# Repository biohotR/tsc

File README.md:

# OpenBook

## Overview

The project was carried out as part of the Computer Systems Testing course and aims to create a detailed 3D model of an E-Book Reader tablet. We worked on both the internal circuit design and the development of the device’s external appearance, using Fusion 360 software provided by Autodesk.

## Bill of Materials
| Componenta | Link | Datasheet |
|-----------|--------------|-----------|
| BUTTON | [Model](https://industry.panasonic.com/global/en/products/control/switch/light-touch/number/evqpuj02k) | [Datasheet](https://www.lcsc.com/datasheet/lcsc_datasheet_2201121800_PANASONIC-EVQPUJ02K_C2936858.pdf) |
| CAPACITOR | [Model](https://componentsearchengine.com/part-view/R0402%201%25%20100%20K%20(RC0402FR-07100KL)/YAGEO) | [Datasheet](//efaidnbmnnnibpcajpcglclefindmkaj/https://www.resistor.com/assets/pdf/0402tstd.pdf) |
| CPH3225A | [Model](https://www.snapeda.com/parts/CPH3225A/Seiko+Instruments/view-part/?ref=eda) | [Datasheet](https://octopart.com/datasheet/cph3225a-seiko-25340571) |
| EVQPUJ02K | [Model](https://industry.panasonic.com/global/en/products/control/switch/light-touch/number/evqpuj02k) | [Datasheet](https://www.lcsc.com/datasheet/lcsc_datasheet_2201121800_PANASONIC-EVQPUJ02K_C2936858.pdf) |
| KP-1608SURCK | [Model](https://www.snapeda.com/parts/KP-1608SURCK/Kingbright/view-part/?ref=search&t=LED%200603) | [Datasheet](//efaidnbmnnnibpcajpcglclefindmkaj/https://media.elv.com/file/107153_led_surck1608_data.pdf) |
| USBLC6-2SC6Y | [Model](https://www.snapeda.com/parts/USBLC6-2SC6Y/STMicroelectronics/view-part/?ref=eda) | [Datasheet](https://www.digikey.com/en/htmldatasheets/production/1375342/0/0/1/usblc6-2sc6y) |
| SD0805S020S1R0 | [Model](https://ro.mouser.com/ProductDetail/KYOCERA-AVX/SD0805S020S1R0?qs=jCA%252BPfw4LHbpkAoSnwrdjw%3D%3D) | [Datasheet](https://www.alldatasheet.com/view.jsp?Searchword=SD0805S&sField=2) |
| PGB1010603MR | [Model](https://www.snapeda.com/parts/PGB1010603MR/Littelfuse/view-part/?ref=eda) | [Datasheet](https://www.alldatasheet.com/view.jsp?Searchword=Pgb1010603mr&gad_source=1&gbraid=0AAAAADcdDU8aYfZtfJfdZ9I5j6RwZ_cbA&gclid=Cj0KCQjwqcO_BhDaARIsACz62vOPBOBe0eOh5gDUFkkKl4JBcbmoFZYtJ8BOnbaWqr_BuUCcVWvbutAaAmGkEALw_wcB) |
| BD5229G-TR  | [Model](https://componentsearchengine.com/part-view/BD5229G-TR/ROHM%20Semiconductor) | [Datasheet](https://www.lcsc.com/datasheet/lcsc_datasheet_2201131330_ROHM-Semicon-BD5229G-TR_C962636.pdf) |
| XC6220A331MR-G | [Model](https://componentsearchengine.com/part-view/XC6220A331MR-G/Torex) | [Datasheet](https://www.alldatasheet.com/view.jsp?Searchword=Xc6220&gad_source=1&gbraid=0AAAAADcdDU8aYfZtfJfdZ9I5j6RwZ_cbA&gclid=Cj0KCQjwqcO_BhDaARIsACz62vPS06NB6tLgniZzfaVpKNu1m811BNk6AEPfg4DbP6f5S8QWA_pW_UQaAv-0EALw_wcB) |
| XC6220A331MR-G | [Model](https://componentsearchengine.com/part-view/XC6220A331MR-G/Torex) | [Datasheet](https://www.alldatasheet.com/view.jsp?Searchword=Xc6220&gad_source=1&gbraid=0AAAAADcdDU8aYfZtfJfdZ9I5j6RwZ_cbA&gclid=Cj0KCQjwqcO_BhDaARIsACz62vMO5_aHsn35cIZBK6oCFuB_WOxz_zKu4yOHJ69-EnaUd5Jfas_Avm8aAuk5EALw_wcB) |
| USB4110-GF-A  | [Model](https://componentsearchengine.com/part-view/USB4110-GF-A/GCT%20(GLOBAL%20CONNECTOR%20TECHNOLOGY)) | [Datasheet](//efaidnbmnnnibpcajpcglclefindmkaj/https://gct.co/files/drawings/usb4110.pdf) |
| Adafruit | [Model](https://eu.mouser.com/ProductDetail/Adafruit/4208?qs=PzGy0jfpSMtbScLbr0L5dw%3D%3D) | [Datasheet](https://www.arrow.com/en/manufacturers/adafruit-industries/datasheets) |
| Bobina | [Model](https://store.comet.srl.ro/Catalogue/Product/43497/) | [Datasheet](https://www.scribd.com/document/814581278/Datasheet-Bobina) |
| PFMF | [Model](https://www.mouser.co.uk/ProductDetail/EPCOS-TDK/B72520T0350K062?qs=dEfas%2FXlABIszF52uu7vrg%3D%3D) | [Datasheet](https://ro.mouser.com/c/ds/circuit-protection/thermistors/resettable-fuses-pptc/?m=Schurter&series=PFMF) |
| DMG2305UX-7 | [Model](https://componentsearchengine.com/part-view/DMG2305UX-7/Diodes%20Incorporated) | [Datasheet](//efaidnbmnnnibpcajpcglclefindmkaj/https://www.mouser.com/datasheet/2/115/DMG2305UX-266242.pdf?srsltid=AfmBOop22k34YTJJra1xubiU6LPiN4M4JlcWbRoSNdxSGFak8uWgXPpK) |
| Si1308EDL-T1-GE3 | [Model](https://componentsearchengine.com/part-view/SI1308EDL-T1-GE3/Vishay) | [Datasheet](https://www.alldatasheet.com/view.jsp?Searchword=Si1308edl&gad_source=1&gbraid=0AAAAADcdDU-px713ONYSnQ2O-gcwqYcFq&gclid=Cj0KCQjwqcO_BhDaARIsACz62vN_Nz3MJOc6J_03gnVBm7aSqC8v9wyP0VD-iRKP-gFrYgdhLi99I14aAlVJEALw_wcB) |
| R0402 | [Model](https://componentsearchengine.com/part-view/R0402%201%25%20100%20K%20(RC0402FR-07100KL)/YAGEO) | [Datasheet](//efaidnbmnnnibpcajpcglclefindmkaj/https://www.resistor.com/assets/pdf/0402tstd.pdf) |
| BME680 | [Model](https://www.snapeda.com/parts/BME680/Bosch/view-part/?welcome=home) | [Datasheet](//efaidnbmnnnibpcajpcglclefindmkaj/https://www.bosch-sensortec.com/media/boschsensortec/downloads/datasheets/bst-bme680-ds001.pdf) |
| SMD Solder | [Model](https://grabcad.com/library/solder-jumpers-1) | [Datasheet]() |
| W25Q512JVEIQ | [Model](https://www.snapeda.com/parts/ESP32-C6-WROOM-1-N8/Espressif+Systems/view-part/?ref=eda) | [Datasheet](//efaidnbmnnnibpcajpcglclefindmkaj/https://www.mouser.com/datasheet/2/949/W25Q512JV_SPI_RevB_06252019_KMS-2487502.pdf?srsltid=AfmBOoquExqDVgxEELF9CzuOGxHos0CD1nQDROHD6Eebdm2foNzqozqU) |
| ESP32-C6-WROOM-1-N8 | [Model](https://www.snapeda.com/parts/ESP32-C6-WROOM-1-N8/Espressif+Systems/view-part/?ref=eda) | [Datasheet](//efaidnbmnnnibpcajpcglclefindmkaj/https://www.mouser.com/catalog/specsheets/Espressif_ESP32_C6_WROOM_1%20_Datasheet_V0.1_PRELIMINARY_en.pdf?srsltid=AfmBOooHQKNitqODRaaPjoZInfWKTacDER1t5uRK6sKqT13TrzvVo_B7) |
| DS3231SN# | [Model](https://www.snapeda.com/parts/DS3231SN%23/Analog+Devices/view-part/?ref=eda) | [Datasheet](https://www.alldatasheet.com/view.jsp?Searchword=Ds3231sn%20datasheet&gad_source=1&gbraid=0AAAAADcdDU-Gy9URfMxGmqiPg7ci5L3wR&gclid=Cj0KCQjwqcO_BhDaARIsACz62vMkK3ETSnW2w7mo0Fa-wgWJGn89AxWCyIND6k5X8MmoPl6hv6VWwT8aAiS-EALw_wcB) |
| MAX17048G+T10 | [Model](https://www.snapeda.com/parts/MAX17048G+T10/Analog+Devices/view-part/?ref=eda) | [Datasheet](https://www.alldatasheet.com/view.jsp?Searchword=Max17048&gad_source=1&gbraid=0AAAAADcdDU8aYfZtfJfdZ9I5j6RwZ_cbA&gclid=Cj0KCQjwqcO_BhDaARIsACz62vNa9xrVfzjCjADRwXD0RBbo4Nret3ywwteDGLJKZui8ZL8KdVlTE7caAvQxEALw_wcB) |
| MCP73831T-5ACI/OT | [Model](https://www.mouser.co.uk/ProductDetail/Microchip-Technology/MCP73831T-5ACI-OT?qs=hH%252BOa0VZEiAcgAcEkuamXg%3D%3D) | [Datasheet](//efaidnbmnnnibpcajpcglclefindmkaj/https://ww1.microchip.com/downloads/en/DeviceDoc/MCP73831-Family-Data-Sheet-DS20001984H.pdf) |

## Hardware Functionality
The designed circuit includes several key components that ensure the full operation of the E-Book Reader:

1. USB-C Connector with ESD Protection
  
 > Responsible for supplying power to the reader via a USB interface, while also incorporating electrostatic discharge protection to ensure safe and stable operation.
 
2. SD Card
 
 > Acts as the primary storage unit for digital books. It functions at 3.3V and interacts with the microcontroller through the SPI communication bus.
 
3. E-Paper Display and supporting modules: Drive Circuit, EPD Header, and Power Module
  
> The EPD connector interfaces with the microcontroller over SPI and links the display to the system. Power is delivered by a dedicated module that provides multiple voltage levels, while the drive circuit generates the waveforms necessary to update the E-Paper screen.
 
4. BME688 Environmental Sensor
  
 > Capable of detecting temperature, humidity, barometric pressure, and air quality. It operates at 3.3V and uses the I2C protocol for data exchange with the microcontroller.

5. DS3231SN Real-Time Clock Module (RTC)
  
 > Maintains accurate timekeeping, even during power loss, thanks to an onboard 32KHz crystal and optional battery backup. Communication is handled via the I2C protocol, connected through the SDA and SCL lines to the ESP32-C6.

6. External 64MB NOR Flash Memory
  
> Provides additional memory space beyond the microcontroller’s internal storage. Suitable for both long-term data retention and temporary caching. It communicates via SPI.

7.	LDO Voltage Regulator
  
> EStabilizes the power supply by delivering a consistent 3.3V output. Its efficiency and low power usage make it well-suited for portable, battery-operated systems.

8. Voltage Supervisor
  
> Ensures the system starts only under safe voltage conditions by continuously monitoring the power supply and blocking startup if voltage levels are insufficient or erratic.

9. Qwiic/Stemma QT Interface
  
> Simplifies sensor and peripheral integration by allowing multiple I2C devices to be linked in series, reducing the need for complex wiring and enabling plug-and-play functionality.

## Microcontroller ESP32-C6
The entire system is built around the ESP32-C6-WROOM microcontroller, a pre-assembled module with a wide range of integrated capabilities.
* The ESP-WROOM-32 board provides a variety of interfaces for connecting external sensors and components. These include I/O pins, SPI, I2C, and UART, which make it highly versatile for different types of applications. It supports Wi-Fi 6 at 2.4 GHz and features Bluetooth 5 along with a built-in antenna for reliable wireless communication.

* The microcontroller interfaces with various peripheral modules using its dedicated pins, each serving specific functions:

### Power and Reset Control
 > The 3V3 pin powers the module, and GND connects to ground. The EN pin must be set to a HIGH level to activate the module and is typically controlled by a reset button.
### USB-C Interface
 > Since the ESP32-C6 has native USB support, the device communicates directly using the USB_D+ and USB_D- lines, which are mapped to GPIO13 and GPIO14 pins. This eliminates the need for an external USB-to-serial converter.
 ### SD Card Module
> The SD card communicates with the ESP32-C6 via the SPI protocol. The necessary pins for this connection are:
GPIO27 (MISO) – data transfer from the card to the microcontroller,
GPIO7 (MOSI) – data sent to the SD card,
GPIO6 (SCK) – clock signal for synchronization,
GPIO4 (SS_SD) – chip select for the SD card.
### E-Ink Display
> The E-Paper display is connected and controlled using the following pins:
GPIO11 (EPD_CS) – chip select for the display,
GPIO5 (EPD_DC) – display control,
GPIO21 (EPD_RST) – reset pin for the display,
GPIO26 (EPD_BUSY) – pin for checking the display status.
### BME688 Environmental Sensor
> The environmental sensor uses the I2C communication protocol. The pins involved are:
GPIO19 (SDA),GPIO20 (SCL),GPIO17 (I2C_PW) – I2C power control pin.
### UART Communication
> The ESP32-C6 also supports UART communication, which is useful for debugging or connecting to other serial devices. The UART pins are:
TXD0 – data transmission,RXD0 – data reception.
### Other Important Pins
> FLASH_CS – This pin is used to select the external NOR Flash memory via the SPI protocol.
> IO/BOOT – Serves to initiate the boot mode, typically activated through a dedicated button.
> RTC_PWM – Generates Pulse Width Modulation (PWM) signals, controlling the Real-Time Clock (RTC) module's operation.
> RTC_RST – Pin responsible for resetting the RTC module, ensuring it starts from a known state.
> INT_RTC – Interrupt pin used by the RTC module, useful for triggering actions such as waking the system from sleep mode or executing periodic tasks like display updates.

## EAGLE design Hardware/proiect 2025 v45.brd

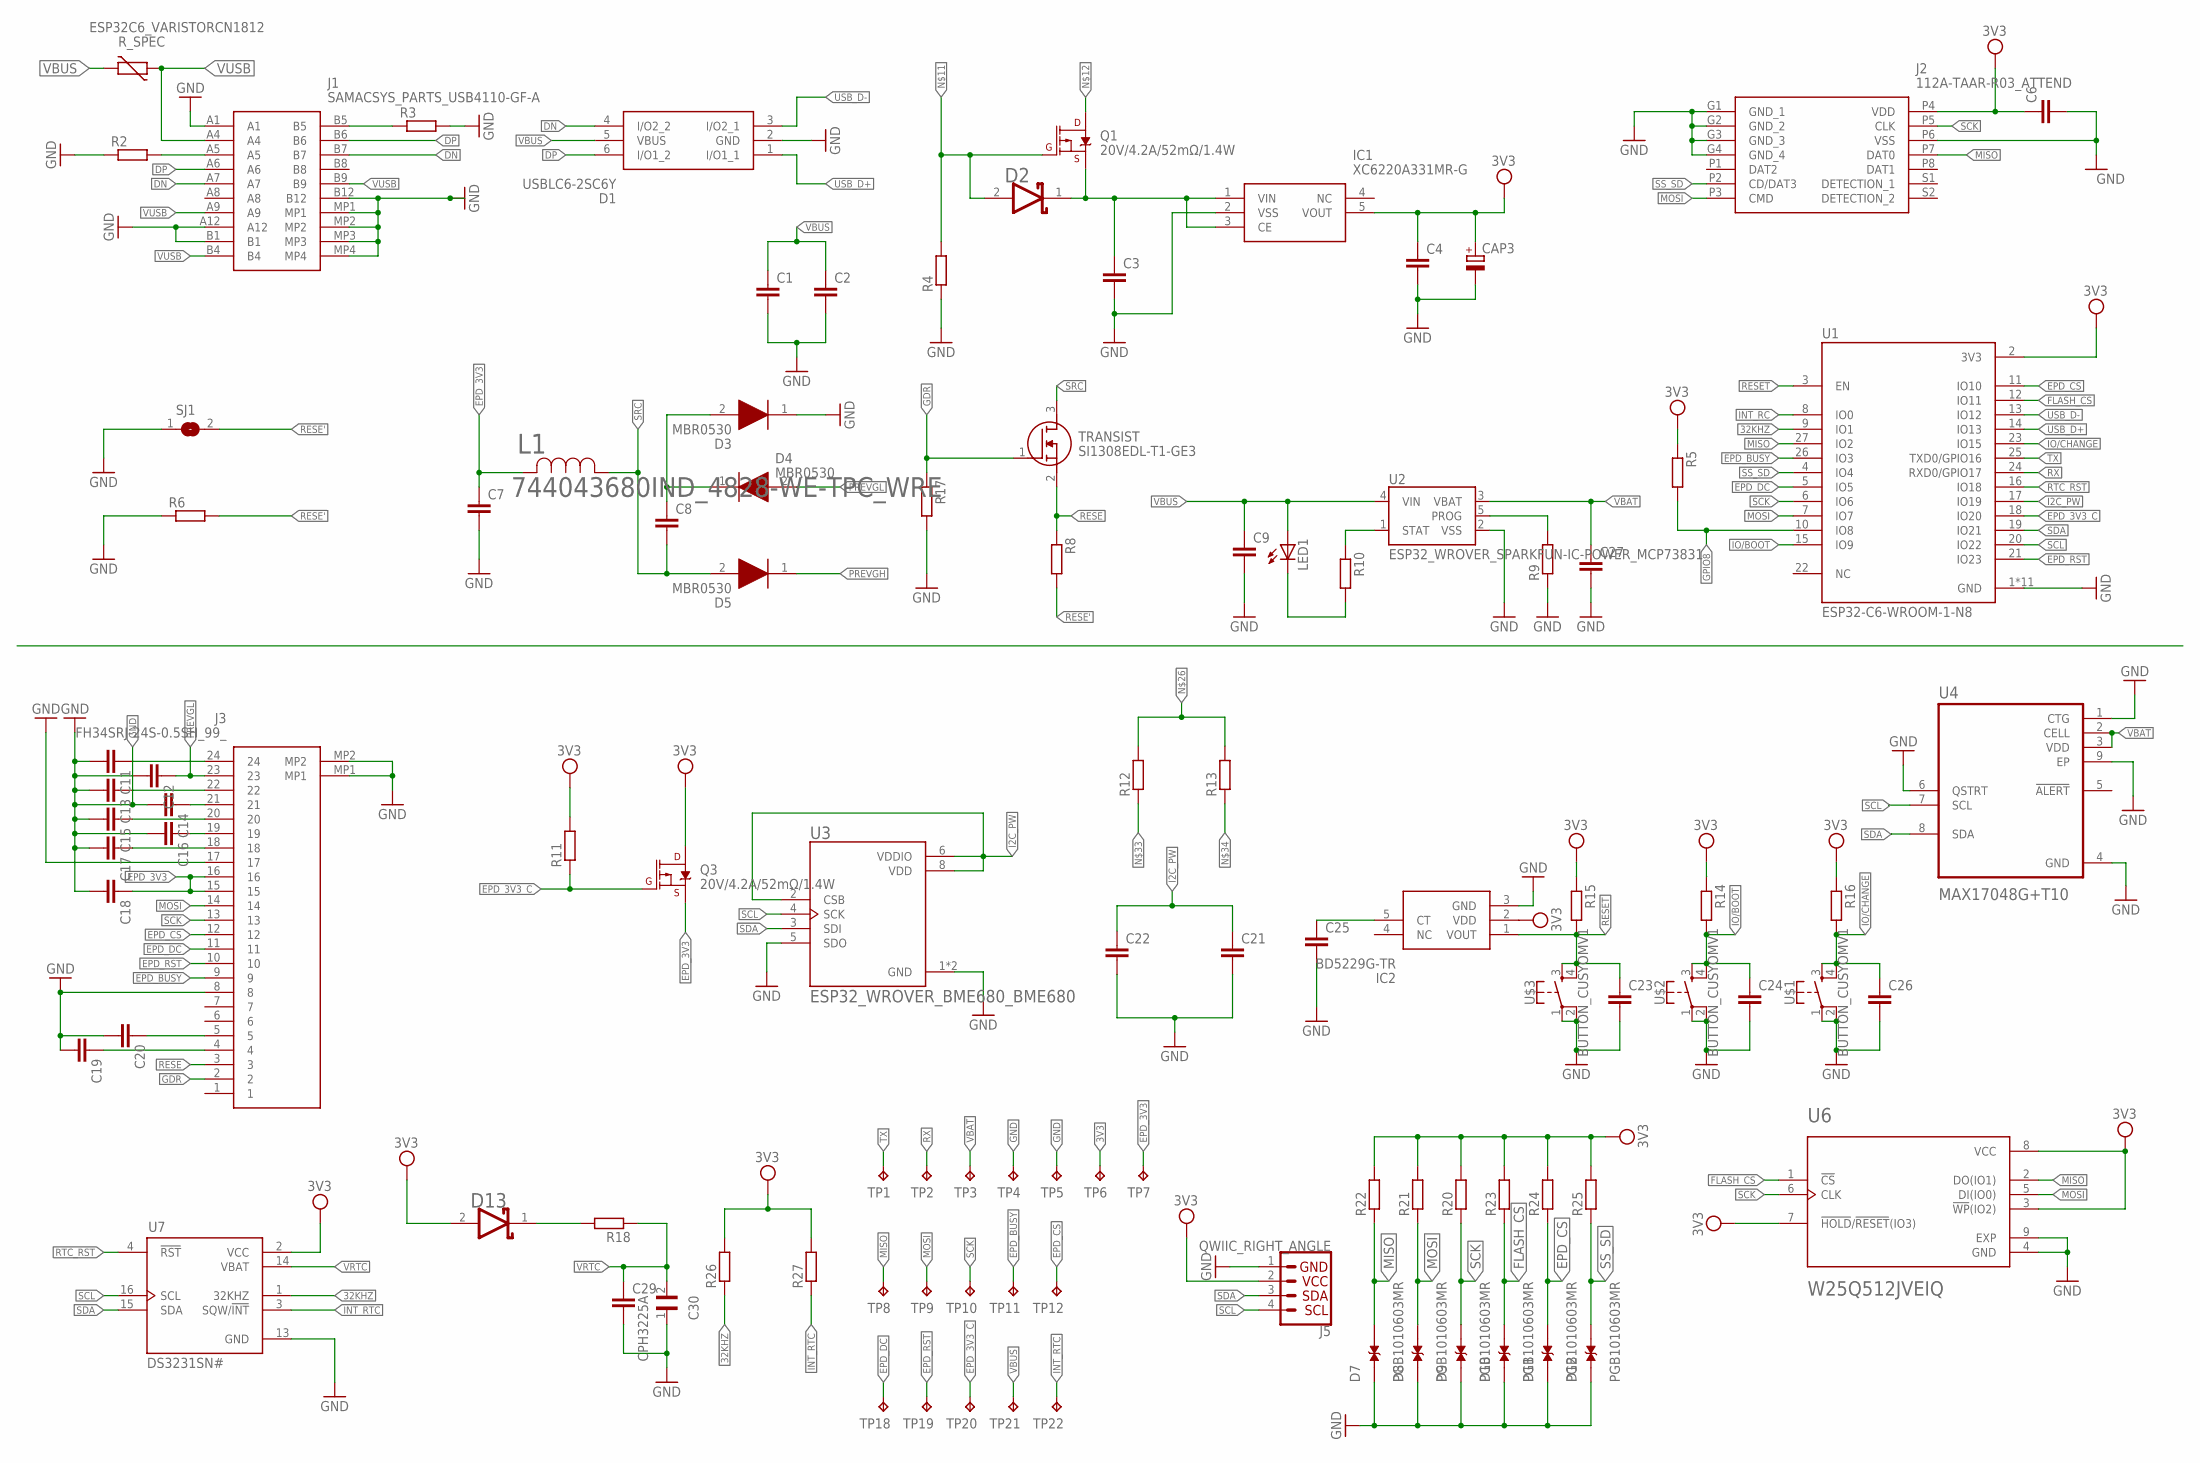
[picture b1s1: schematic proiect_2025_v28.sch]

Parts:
C1, C2, C3, C4, C6, C7, C8, C9, C11, C12, C13, C14, C15, C16, C17, C18, C19, C20, C21, C22, C25, C27, C29: ESP32_WROVER_EAGLE-LTSPICE_CC0402; ESP32_WROVER_EAGLE-LTSPICE_C0402
C23, C24, C26: EAGLE-LTSPICE_CC0402; EAGLE-LTSPICE_C0402
C30: CPH3225A; CAPCP3225X100N
CAP3: RCL_CPOL-EUCT3528; RCL_CT3528
D1: USBLC6-2SC6Y; SOT95P280X145-6N
D2, D13: ESP32_WROVER_AVX---SD0805S020S1R0_AVX_SD0805S020S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; ESP32_WROVER_AVX---SD0805S020S1R0_AVX_SD0805S020S1R0_0
D3, D4, D5: MBR0530; SOD3716X135N
D7, D8, D9, D10, D11, D12: PGB1010603MR; DIOC1608X36N
IC1: XC6220A331MR-G; SOT95P280X120-5N
IC2: BD5229G-TR; SOT95P280X125-5N
J1: SAMACSYS_PARTS_USB4110-GF-A; SAMACSYS_PARTS_USB4110GFA
J2: 112A-TAAR-R03_ATTEND; 112ATAARR03ATTEND
J3: FH34SRJ-24S-0.5SH_99_; FH34SRJ24S05SH99
J5: QWIIC_RIGHT_ANGLE; JST04_1MM_RA
L1: 744043680IND_4828-WE-TPC_WRE; IND_4828-WE-TPC_WRE
LED1: ADAFRUIT_LEDCHIP-LED0603; ADAFRUIT_CHIP-LED0603
Q1, Q3: 20V/4.2A/52mΩ/1.4W; ESP32_WROVER_SPARKFUN-DISCRETESEMI_SOT23-3
R2, R3, R4, R5, R6, R8, R9, R10, R11, R12, R13, R14, R15, R16, R17, R18, R20, R21, R22, R23, R24, R25, R26, R27: ESP32_WROVER_EAGLE-LTSPICE_RR0402; ESP32_WROVER_EAGLE-LTSPICE_R0402
R_SPEC: ESP32C6_VARISTORCN1812; ESP32C6_VARISTOR_CT/CN1812
SJ1: SJ
TP1, TP2, TP3, TP4, TP5, TP6, TP7, TP8, TP9, TP10, TP11, TP12, TP18, TP19, TP20, TP21, TP22: TPTP20R; TP20R
TRANSIST: SI1308EDL-T1-GE3; SOT65P210X110-3N
U1: ESP32-C6-WROOM-1-N8; XCVR_ESP32-C6-WROOM-1-N8
U2: ESP32_WROVER_SPARKFUN-IC-POWER_MCP73831; ESP32_WROVER_SPARKFUN-IC-POWER_SOT23-5
U3: ESP32_WROVER_BME680_BME680; ESP32_WROVER_BME680_PSON80P300X300X100-8N
U4: MAX17048G+T10; SON50P200X200X80-9N
U6: W25Q512JVEIQ; SON127P600X800X80-9N
U7: DS3231SN#; SOIC127P1032X265-16N
U$1, U$2, U$3: BUTTON_CUSYOMV1; MYBUTTON

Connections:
3V3: C4.1, C6.1, CAP3.+, D13.2 (ANODE), IC1.5 (VOUT), IC2.2 (VDD), J2.P4 (VDD), J5.2, Q3.3 (D), R5.1, R11.2, R14.1, R15.1, R16.1, R20.2, R21.2, R22.2, R23.2, R24.2, R25.2, R26.2, R27.2, TP6.TP, U1.2 (3V3), U6.3 (!WP!(IO2)), U6.7 (!HOLD!/!RESET!(IO3)), U6.8 (VCC), U7.2 (VCC)
32KHZ: R26.1, U1.9 (IO1), U7.1 (32KHZ)
DN: D1.4 (I/O2_2), J1.B7
DP: D1.6 (I/O1_2), J1.A6, J1.B6
EPD_3V3: C7.1, C18.1, J3.15, J3.16, L1.2, Q3.2 (S), TP7.TP
EPD_3V3_C: Q3.1 (G), R11.1, TP20.TP, U1.18 (IO20)
EPD_BUSY: J3.9, TP11.TP, U1.26 (IO3)
EPD_CS: D11.2, J3.12, R24.1, TP12.TP, U1.11 (IO10)
EPD_DC: J3.11, TP18.TP, U1.5 (IO5)
EPD_RST: J3.10, TP19.TP, U1.21 (IO23)
FLASH_CS: D10.2, R23.1, U1.12 (IO11), U6.1 (!CS)
GDR: J3.2, R17.1, TRANSIST.1 (G)
GND: C1.2, C2.2, C3.2, C4.2, C6.2, C7.2, C9.2, C11.2, C12.2, C13.2, C14.2, C15.2, C16.2, C17.2, C18.2, C19.2, C20.2, C21.2, C22.2, C23.2, C24.2, C25.2, C26.2, C27.2, C29.2, C30.1, CAP3.-, D1.2 (GND), D3.1 (K), D7.1, D8.1, D9.1, D10.1, D11.1, D12.1, IC1.2 (VSS), IC2.3 (GND), J1.A1, J1.A12, J1.B1, J1.B12, J1.MP1, J1.MP2, J1.MP3, J1.MP4, J2.G1 (GND_1), J2.G2 (GND_2), J2.G3 (GND_3), J2.G4 (GND_4), J2.P6 (VSS), J3.8, J3.17, J3.MP1, J3.MP2, J5.1, R2.1, R3.2, R4.1, R6.1, R9.1, R17.2, SJ1.1, TP4.TP, TP5.TP, U1.1 (GND), U1.28 (GND), U1.29_1 (GND), U1.29_2 (GND), U1.29_3 (GND), U1.29_4 (GND), U1.29_5 (GND), U1.29_6 (GND), U1.29_7 (GND), U1.29_8 (GND), U1.29_9 (GND), U2.2 (VSS), U3.1 (GND), U3.5 (SDO), U3.7 (GND), U4.1 (CTG), U4.4 (GND), U4.6 (QSTRT), U4.9 (EP), U6.4 (GND), U6.9 (EXP), U7.13 (GND), U$1.1, U$1.2, U$2.1, U$2.2, U$3.1, U$3.2
GPIO8: R5.2, U1.10 (IO8)
I2C_PW: C21.1, C22.1, U1.17 (IO19), U3.2 (CSB), U3.6 (VDDIO), U3.8 (VDD)
INT_RC: U1.8 (IO0)
INT_RTC: R27.1, TP22.TP, U7.3 (SQW/!INT)
IO/BOOT: C24.1, R14.2, U1.15 (IO9), U$2.3, U$2.4
IO/CHANGE: C26.1, R16.2, U1.23 (IO15), U$1.3, U$1.4
MISO: D7.2, J2.P7 (DAT0), R22.1, TP8.TP, U1.27 (IO2), U6.2 (DO(IO1))
MOSI: D8.2, J2.P3 (CMD), J3.14, R21.1, TP9.TP, U1.7 (IO7), U6.5 (DI(IO0))
unnamed: J1.B5, R3.1
unnamed: J1.A5, R2.2
unnamed: C8.1, D3.2 (A), D4.1 (K)
unnamed: D2.2 (ANODE), Q1.1 (G), R4.2
unnamed: C3.1, D2.1 (CATHODE), IC1.1 (VIN), IC1.3 (CE), Q1.2 (S)
unnamed: C25.1, IC2.5 (CT)
unnamed: LED1.C, R10.2
unnamed: R10.1, U2.1 (STAT)
unnamed: R9.2, U2.5 (PROG)
unnamed: R12.2, R13.2
unnamed: C20.1, J3.5
unnamed: C11.1, J3.24
unnamed: C19.1, J3.4
unnamed: C13.1, J3.22
unnamed: D13.1 (CATHODE), R18.2
unnamed: C14.1, J3.21
unnamed: C15.1, J3.20
unnamed: C16.1, J3.19
unnamed: C17.1, J3.18
PREVGH: D5.1 (K)
PREVGL: C12.1, D4.2 (A), J3.23
RESE: J3.3, R8.1, TRANSIST.2 (S)
RESE': R6.2, R8.2, SJ1.2
RESET: C23.1, IC2.1 (VOUT), R15.2, U1.3 (EN), U$3.3, U$3.4
RTC_RST: U1.16 (IO18), U7.4 (!RST)
RX: TP2.TP, U1.24 (RXD0/GPIO17)
SCK: D9.2, J2.P5 (CLK), J3.13, R20.1, TP10.TP, U1.6 (IO6), U6.6 (CLK)
SCL: J5.4, U1.20 (IO22), U3.4 (SCK), U4.7 (SCL), U7.16 (SCL)
SDA: J5.3, U1.19 (IO21), U3.3 (SDI), U4.8 (SDA), U7.15 (SDA)
SRC: C8.2, D5.2 (A), L1.1, TRANSIST.3 (D)
SS_SD: D12.2, J2.P2 (CD/DAT3), R25.1, U1.4 (IO4)
TX: TP1.TP, U1.25 (TXD0/GPIO16)
USB_D+: D1.1 (I/O1_1), U1.14 (IO13)
USB_D-: D1.3 (I/O2_1), U1.13 (IO12)
VBAT: C27.1, TP3.TP, U2.3 (VBAT), U4.2 (CELL), U4.3 (VDD)
VBUS: C1.1, C2.1, C9.1, D1.5 (VBUS), LED1.A, R_SPEC.2, TP21.TP, U2.4 (VIN)
VRTC: C29.1, C30.2, R18.1, U7.14 (VBAT)
VUSB: J1.A4, J1.A9, J1.B4, J1.B9, R_SPEC.1

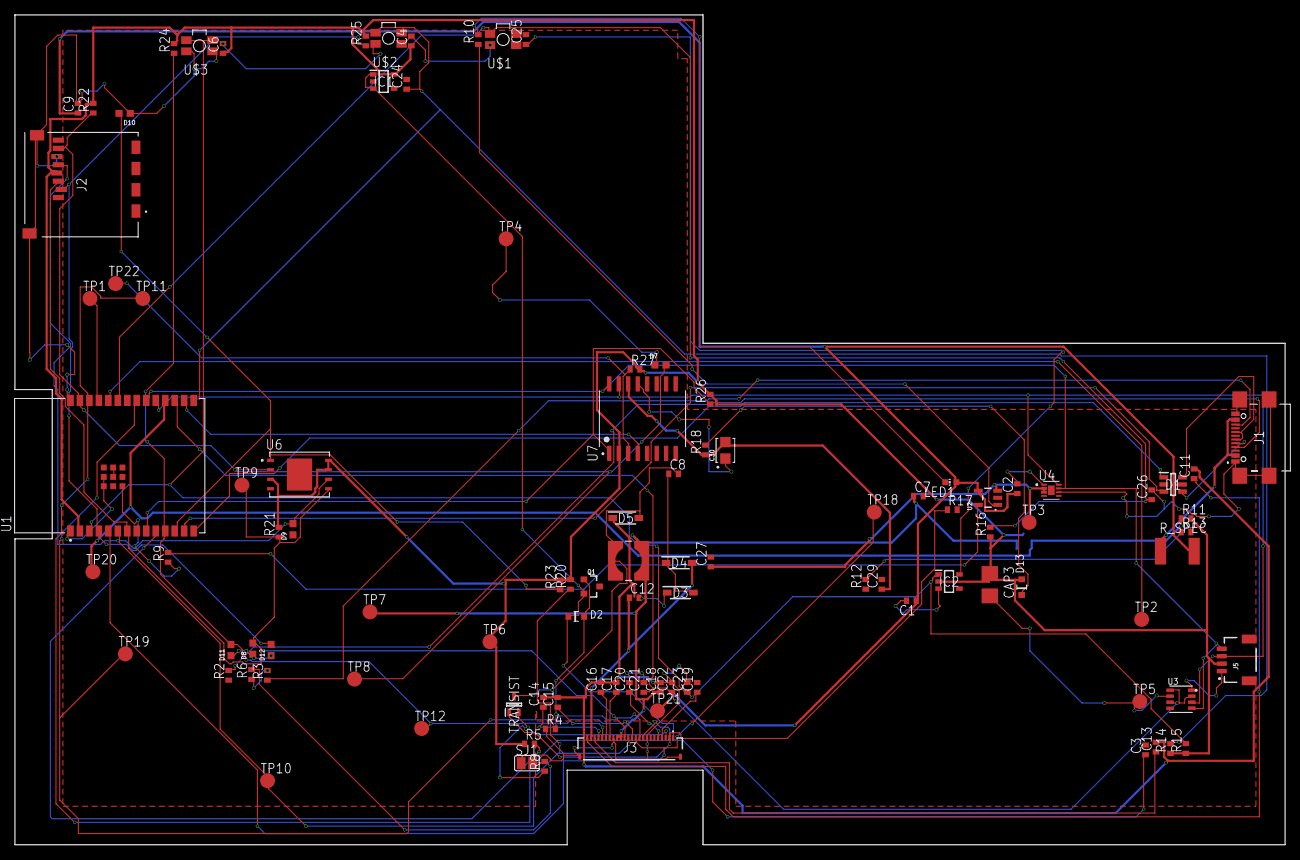
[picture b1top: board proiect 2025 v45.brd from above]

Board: 2 copper layers, 170.2 x 111.2 mm, 103 parts (1 on the bottom side), 57 nets.

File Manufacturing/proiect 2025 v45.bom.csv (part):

Qty,Value,Device,Package,Parts,Description,ARROW_PART_NUMBER,ARROW_PRICE-STOCK,AVAILABILITY,CENTROID_NOT_SPECIFIED,CHECK_PRICES,COPYRIGHT,DATASHEET,DESCRIPTION,DIGIKEY_DESCRIPTION,DIGIKEY_PART_NUMBER,HEIGHT,LEAD_FREE,MANUFACTURER_NAME,MANUFACTURER_PART_NUMBER,MF,MFR_NAME,MOUSER_PART_NUMBER,MOUSER_PRICE-STOCK,MOUSER_TESTING_PART_NUMBER,MOUSER_TESTING_PRICE-STOCK,MP,MPN,PACKAGE,POPULARITY,PREFIX,PRICE,PROD_ID,PURCHASE-URL,ROHS,SNAPEDA_LINK,SPICEMODEL,SPICEPREFIX,TEMPERATURE_RANGE_HIGH,TEMPERATURE_RANGE_LOW,TP_SIGNAL_NAME,VALUE
1,,ADAFRUIT_LEDCHIP-LED0603,ADAFRUIT_CHIP-LED0603,LED1,LED,,,,,,,,,,,,,,,,,,,,,,,,,,,,,,,,,,,,
3,,EAGLE-LTSPICE_CC0402,EAGLE-LTSPICE_C0402,"C23, C24, C26","CAPACITOR, European symbol",,,,,,,,,,,,,,,,,,,,,,,,,,,,,,,NONE,C,,,,
23,,ESP32_WROVER_EAGLE-LTSPICE_CC0402,ESP32_WROVER_EAGLE-LTSPICE_C0402,"C1, C2, C3, C4, C6, C7, C8, C9, C11, C12, C13, C14, C15, C16, C17, C18, C19, C20, C21, C22, C25, C27, C29","CAPACITOR, European symbol",,,,,,,,,,,,,,,,,,,,,,,,,,,,,,,NONE,C,,,,
24,,ESP32_WROVER_EAGLE-LTSPICE_RR0402,ESP32_WROVER_EAGLE-LTSPICE_R0402,"R2, R3, R4, R5, R6, R8, R9, R10, R11, R12, R13, R14, R15, R16, R17, R18, R20, R21, R22, R23, R24, R25, R26, R27","RESISTOR, European symbol",,,,,,,,,,,,,,,,,,,,,,,,,,,,,,,NONE,R,,,,
1,,RCL_CPOL-EUCT3528,RCL_CT3528,CAP3,"POLARIZED CAPACITOR, European symbol",,,,,,,,,,,,,,,,,,,,,,,,0,,,,,,,,C,,,,
1,,SJ,SJ,SJ1,"SMD solder JUMPER",,,,,,,,,,,,,,,,,,,,,,,,3,,,,,,,,,,,,
1,112A-TAAR-R03_ATTEND,112A-TAAR-R03_ATTEND,112ATAARR03ATTEND,J2,"Micro SD Card Socket, Push-Push Type, Top Mount, SMT, H=1.83mm, 10u",,,,,,,,"Micro SD Card Socket"," Push-Push Type"," Top Mount"," SMT"," H=1.83mm"," 10u",,,1.9mm,,ATTEND,"112A-TAAR-R03 ATTEND",,,,,,,,,,,,,,,,,
2,20V/4.2A/52mΩ/1.4W,ESP32_WROVER_SPARKFUN-DISCRETESEMI_MOSFET_PCH-DMG2305UX-7,ESP32_WROVER_SPARKFUN-DISCRETESEMI_SOT23-3,"Q1, Q3","P-channel MOSFETs",,,,,,,,,,,,,,,,,,,,,,,,,,,TRAN-14388,,,,,,,,,20V/4.2A/52mΩ/1.4W
1,744043680IND_4828-WE-TPC_WRE,744043680IND_4828-WE-TPC_WRE,IND_4828-WE-TPC_WRE,L1,,,,,,,"Copyright (C) 2024 Ultra Librarian. All rights reserved.",,,,,,,,744043680,,"Wurth Electronics",,,,,,,,,,,,,,,,,,,,
1,BD5229G-TR,BD5229G-TR,SOT95P280X125-5N,IC2,"Voltage Detector with Adjustable Delay Time: CMOS processes are utilized to develop high precision, low current consumption CMOS reset ICs that allow arbitrary setting of the delay time. The extensive lineup includes both Nch Open Drain and CMOS output types in a wide range of detection voltages (from 2.3V to 6.0V, in 0.1V steps), enabling selection of the ideal solution based on customer requirements. In addition, the entire series is of course both lead-free and RoHS-compliant.",,,,,,,,"Voltage Detector with Adjustable Delay Time: CMOS processes are utilized to develop high precision"," low current consumption CMOS reset ICs that allow arbitrary setting of the delay time. The extensive lineup includes both Nch Open Drain and CMOS output types in a wide range of detection voltages (from 2.3V to 6.0V"," in 0.1V steps)"," enabling selection of the ideal solution based on customer requirements. In addition"," the entire series is of course both lead-free and RoHS-compliant.",,,1.25mm,,"ROHM Semiconductor",BD5229G-TR,,,755-BD5229G-TR,https://www.mouser.co.uk/ProductDetail/ROHM-Semiconductor/BD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,,,,,,,,,,,,,,
3,BUTTON_CUSYOMV1,BUTTON_CUSYOMV1,MYBUTTON,"U$1, U$2, U$3",,,,,,,,,,,,,,,,,,,,,,,,,,,,,,,,,,,,,
1,CPH3225A,CPH3225A,CAPCP3225X100N,C30,"Cap 0.011F 3.3V 1210 Flat Check availability",,,"Not in stock",,https://www.snapeda.com/parts/CPH3225A/Seiko+Instruments/vie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,,," 11 mF (EDLC) Supercapacitor 3.3 V 1210 (3225 Metric) - - ",,,,,,,"Seiko Instruments",,,,,,CPH3225A,,"1210 Seiko",,,None,,"https://www.snapeda.com/api/url_track_click_mouser/?unipart_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 Instruments&part_name=CPH3225A&search_term=None",,https://www.snapeda.com/parts/CPH3225A/Seiko+Instruments/vie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,,,,,,
1,DS3231SN#,DS3231SN#,SOIC127P1032X265-16N,U7,"Real Time Clock Serial 16-Pin SOIC W T/R     Check availability",,,"In Stock",,https://www.snapeda.com/parts/DS3231SN%23/Analog+Devices/vie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,,," Extremely Accurate I²C-Integrated RTC/TCXO/Crystal ",,,,,,,"Analog Devices",,,,,,DS3231SN#,,"SOIC-16 Maxim",,,None,,"https://www.snapeda.com/api/url_track_click_mouser/?unipart_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 Devices&part_name=DS3231SN#&search_term=None",,https://www.snapeda.com/parts/DS3231SN%23/Analog+Devices/vie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,,,,,,
1,ESP32-C6-WROOM-1-N8,ESP32-C6-WROOM-1-N8,XCVR_ESP32-C6-WROOM-1-N8,U1,"Check availability",,,"In Stock",,https://www.snapeda.com/parts/ESP32-C6-WROOM-1-N8/Espressif+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,,," Multiprotocol Modules ESP32-C6 module"," Wi-Fi 6 in 2.4 GHz band"," Bluetooth 5"," Zigbee 3.0 and Thread. ESP34-WROOM Compatible - ENGINEERING SAMPLE ",,,,,,,"Espressif Systems",,,,,,ESP32-C6-WROOM-1-N8,,None,,,None,,,,https://www.snapeda.com/parts/ESP32-C6-WROOM-1-N8/Espressif+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,,,
1,ESP32C6_VARISTORCN1812,ESP32C6_VARISTORCN1812,ESP32C6_VARISTOR_CT/CN1812,R_SPEC,VARISTOR,,,,,,,,,,,,,,,,,,,,,,,,0,,,,,,,,,,,,
2,ESP32_WROVER_AVX---SD0805S020S1R0_AVX_SD0805S020S1R0_0_0AVX_SD0805S020S1R0_0_0,ESP32_WROVER_AVX---SD0805S020S1R0_AVX_SD0805S020S1R0_0_0AVX_SD0805S020S1R0_0_0,ESP32_WROVER_AVX---SD0805S020S1R0_AVX_SD0805S020S1R0_0,"D2, D13","Schottky Barrier Rectifier Diode",,,,No,,,http://datasheets.avx.com/schottky.pdf,,"DIODE SCHOTTKY 20V 1A 0805",478-7800-1-ND,,yes,,,AVX,,581-SD0805S020S1R0,,,,,,"0805 (2012 metric)",,D,,,,yes,,,,+125°C,-55°C,,
1,ESP32_WROVER_BME680_BME680,ESP32_WROVER_BME680_BME680,ESP32_WROVER_BME680_PSON80P300X300X100-8N,U3,"Integrated Environmental Unit",,,Unavailable,,,,," Integrated Environmental Unit ",,,,,,,"Bosch Sensortec",,,,,,BME680,,"LGA-8 Bosch Tools",,,None,,,,,,,,,,
1,ESP32_WROVER_SPARKFUN-IC-POWER_MCP73831,ESP32_WROVER_SPARKFUN-IC-POWER_MCP73831,ESP32_WROVER_SPARKFUN-IC-POWER_SOT23-5,U2,"MCP73831T Li-Ion, Li-Pol Controller",,,,,,,,,,,,,,,,,,,,,,,,,,,IC-09995,,,,,,,,,
1,FH34SRJ-24S-0.5SH_99_,FH34SRJ-24S-0.5SH_99_,FH34SRJ24S05SH99,J3," (0.50mm) Surface Mount, Right Angle",,,,,,,,"24 Position FFC"," FPC Connector Contacts"," (0.50mm) Surface Mount"," Right Angle",,,1.1mm,,Hirose,FH34SRJ-24S-0.5SH(99),,,798-FH34SRJ24S05SH99,https://www.mouser.co.uk/ProductDetail/Hirose-Connector/FH34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,,,,,,,,,,,,,,,
1,MAX17048G+T10,MAX17048G+T10,SON50P200X200X80-9N,U4,"Check availability",,,"In Stock",,https://www.snapeda.com/parts/MAX17048G+T10/Analog+Devices/v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,,," 3µA 1-Cell/2-Cell Fuel Gauge with ModelGauge ",,,,,,,"Analog Devices",,,,,,MAX17048G+T10,,"TDFN-8 Maxim",,,None,,"https://www.snapeda.com/api/url_track_click_mouser/?unipart_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 Devices&part_name=MAX17048G+T10&search_term=None",,https://www.snapeda.com/parts/MAX17048G+T10/Analog+Devices/v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,,,,,,
3,MBR0530,MBR0530,SOD3716X135N,"D3, D4, D5","ON SEMICONDUCTOR - MBR0530 - DIODE, SCHOTTKY, 0.5A, 30V, SOD-123",,,"In Stock",,https://www.snapeda.com/parts/MBR0530/Onsemi/view-part/?ref=eda,,," Diode Schottky 30 V 500mA Surface Mount SOD-123 ",,,,,,,"ON Semiconductor",,,,,,MBR0530,,"SOD-123-2 ON Semiconductor",,,None,,"https://www.snapeda.com/api/url_track_click_mouser/?unipart_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 Semiconductor&part_name=MBR0530&search_term=None",,https://www.snapeda.com/parts/MBR0530/Onsemi/view-part/?ref=snap,,,,,,
6,PGB1010603MR,PGB1010603MR,DIOC1608X36N,"D7, D8, D9, D10, D11, D12","Check availability",,,"In Stock",,https://www.snapeda.com/parts/PGB1010603MR/Littelfuse/view-p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,,," 150V (Typ) Clamp - Ipp Tvs Diode Surface Mount 0603 (1608 Metric) ",,,,,,,"Littelfuse Inc.",,,,,,PGB1010603MR,,"0603 Littelfuse Inc.",,,None,,"https://www.snapeda.com/api/url_track_click_mouser/?unipart_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 Inc.&part_name=PGB1010603MR&search_term=None",,https://www.snapeda.com/parts/PGB1010603MR/Littelfuse/view-p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,,,,,,
1,QWIIC_RIGHT_ANGLE,QWIIC_CONNECTORJS-1MM,JST04_1MM_RA,J5,"SparkFun I2C Standard Qwiic Connector",,,,,,,,,,,,,,,,,,,,,,,,,,,CONN-13694,,,,,,,,,QWIIC_RIGHT_ANGLE
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
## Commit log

2025-04-07 basic proj

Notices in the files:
parts and their libraries:
COPYRIGHT: Copyright (C) 2024 Ultra Librarian. All rights reserved.
